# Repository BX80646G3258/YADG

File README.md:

# Yet Another Dogshit Gamepad
YADG is an open source gamepad built on the Arduino platform.
## Features
- 1000hz polling rate
- Polar joystick input
- Curve map
- Configurable deadzones
- Button remapping
- Button debounce settings
- idk what people care about lol
## Images

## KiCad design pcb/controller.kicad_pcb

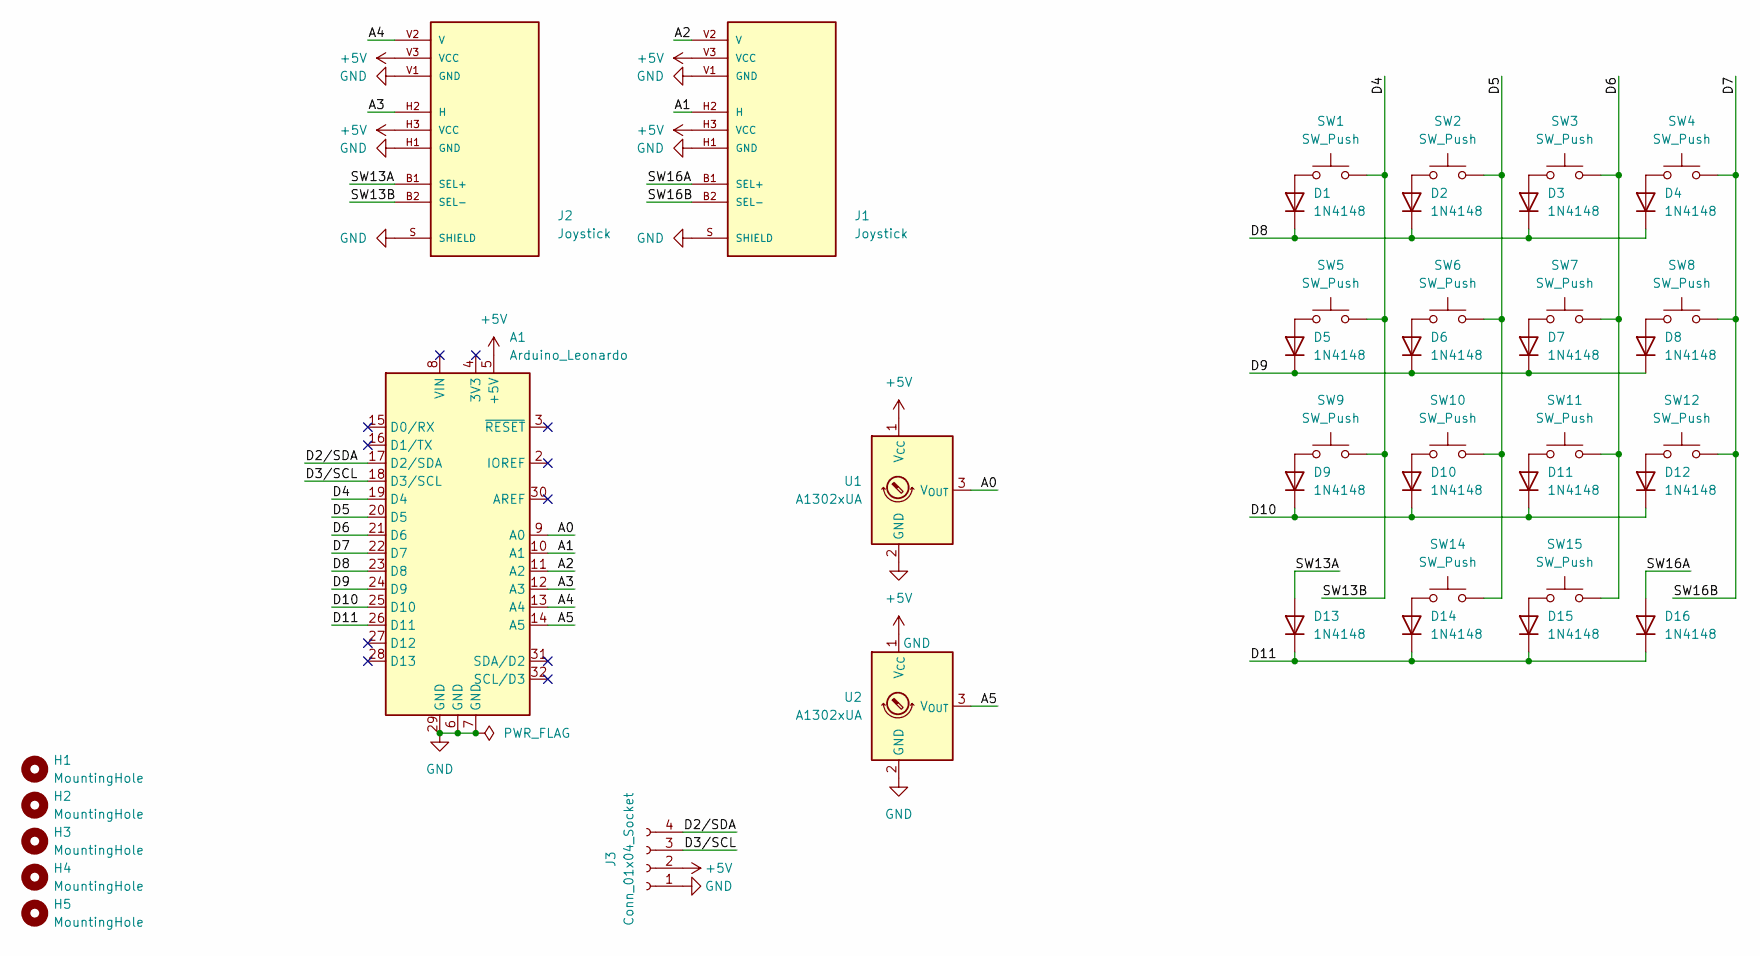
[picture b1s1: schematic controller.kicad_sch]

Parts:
A1: Arduino_Leonardo; Arduino_UNO_R3
D1, D2, D3, D4, D5, D6, D7, D8, D9, D10, D11, D12, D13, D14, D15, D16: 1N4148; D_DO-35_SOD27_P7.62mm_Horizontal
H1, H2, H3, H4, H5: MountingHole; MountingHole_2.2mm_M2_custom
J1, J2: Joystick
J3: Conn_01x04_Socket; JST_XH_B4B-XH-A_1x04_P2.50mm_Vertical
SW1, SW2, SW3, SW4, SW5, SW6, SW7, SW8, SW9, SW10, SW11, SW12: SW_Push; SW_PUSH_6mm_H5mm
SW14, SW15: SW_Push; SW_Tactile_SKHH_Angled
U1, U2: A1302xUA; TO-92S

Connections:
+5V: A1.5 (+5V), J1.H3 (VCC), J1.V3 (VCC), J2.H3 (VCC), J2.V3 (VCC), J3.2, U1.1 (V_{CC}), U2.1 (V_{CC})
/A0: A1.9 (A0), U1.3 (V_{OUT})
/A1: A1.10 (A1), J1.H2 (H)
/A2: A1.11 (A2), J1.V2 (V)
/A3: A1.12 (A3), J2.H2 (H)
/A4: A1.13 (A4), J2.V2 (V)
/A5: A1.14 (A5), U2.3 (V_{OUT})
/D2/SDA: A1.17 (D2/SDA), J3.4
/D3/SCL: A1.18 (D3/SCL), J3.3
/D4: A1.19 (D4), J2.B2 (SEL-), SW1.2, SW5.2, SW9.2
/D5: A1.20 (D5), SW2.2, SW6.2, SW10.2, SW14.2
/D6: A1.21 (D6), SW3.2, SW7.2, SW11.2, SW15.1
/D7: A1.22 (D7), J1.B2 (SEL-), SW4.2, SW8.2, SW12.2
/D8: A1.23 (D8), D1.1 (K), D2.1 (K), D3.1 (K), D4.1 (K)
/D9: A1.24 (D9), D5.1 (K), D6.1 (K), D7.1 (K), D8.1 (K)
/D10: A1.25 (D10), D9.1 (K), D10.1 (K), D11.1 (K), D12.1 (K)
/D11: A1.26 (D11), D13.1 (K), D14.1 (K), D15.1 (K), D16.1 (K)
/SW13A: D13.2 (A), J2.B1 (SEL+)
/SW16A: D16.2 (A), J1.B1 (SEL+)
GND: A1.6 (GND), A1.7 (GND), A1.29 (GND), J1.H1 (GND), J1.S (SHIELD), J1.V1 (GND), J2.H1 (GND), J2.S (SHIELD), J2.V1 (GND), J3.1, U1.2 (GND), U2.2 (GND)
unnamed: D1.2 (A), SW1.1
unnamed: D2.2 (A), SW2.1
unnamed: D3.2 (A), SW3.1
unnamed: D4.2 (A), SW4.1
unnamed: D5.2 (A), SW5.1
unnamed: D6.2 (A), SW6.1
unnamed: D7.2 (A), SW7.1
unnamed: D8.2 (A), SW8.1
unnamed: D9.2 (A), SW9.1
unnamed: D10.2 (A), SW10.1
unnamed: D11.2 (A), SW11.1
unnamed: D12.2 (A), SW12.1
unnamed: D14.2 (A), SW14.1
unnamed: D15.2 (A), SW15.2

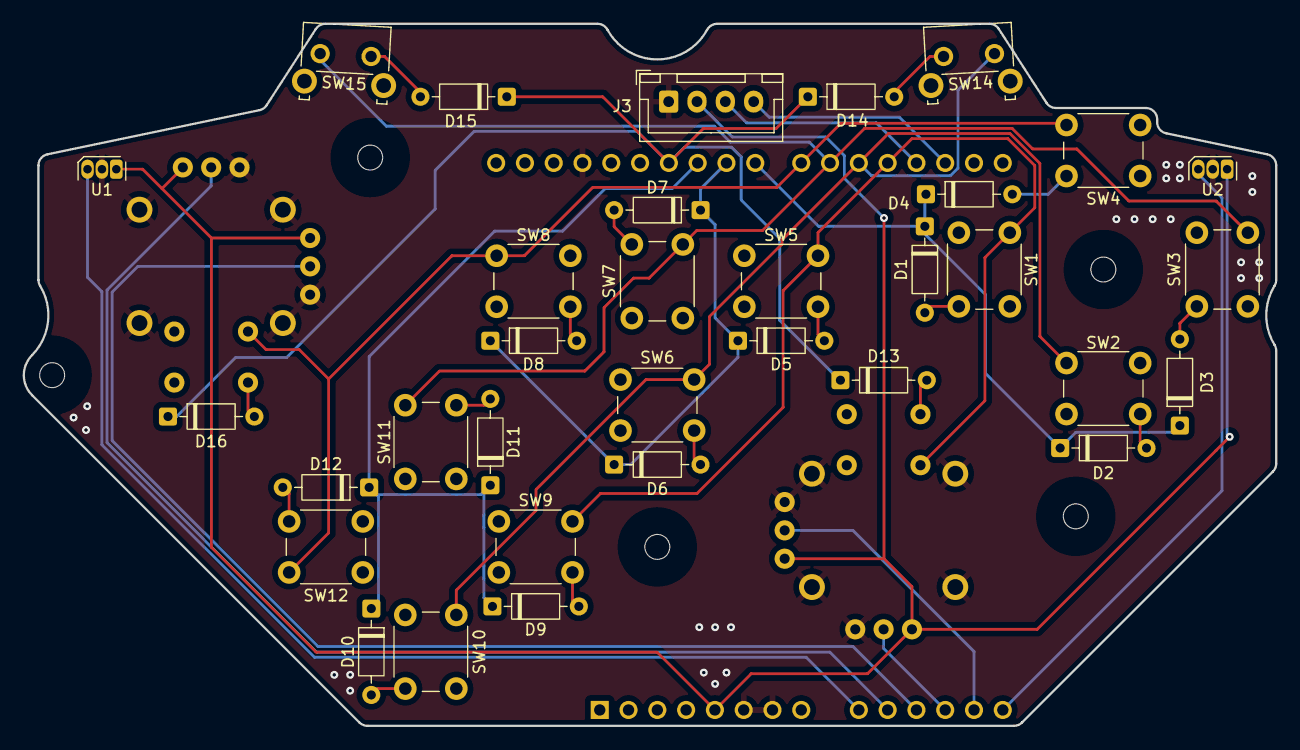
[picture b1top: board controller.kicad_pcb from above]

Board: 2 copper layers, 110.5 x 61.9 mm, 41 parts (1 on the bottom side), 34 nets.

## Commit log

2025-11-19 check for invalid register before row write
2025-11-19 remove unused code
2025-11-19 fix unsigned subtraction
2025-11-19 fix style
2025-11-19 make default max theta more readable
2025-12-01 add images
2025-12-01 added features and images sections
